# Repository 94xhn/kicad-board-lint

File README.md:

# kicad-board-lint

A zero-dependency linter for the board problems **KiCad's DRC silently
accepts**: copper pads with no net, duplicate pads that disagree about their
net, and power tracks too thin for their current. No KiCad installation, no
pcbnew bindings — it parses `.kicad_pcb` / `.kicad_pro` directly, so it runs
anywhere Python runs, including CI.

[中文简介](#中文简介) below. Part of a small family of KiCad lint tools:
[kicad-corner-lint](https://github.com/94xhn/kicad-corner-lint) ·
[kicad-file-doctor](https://github.com/94xhn/kicad-file-doctor).

```text
$ kicad-board-lint examples/demo.kicad_pcb
examples/demo.kicad_pcb: 4 footprints, 4 segments - 4 error(s), 1 warning(s)
  ERROR   dup-pad-net     SW1: duplicate pads "1" disagree about their net: "COL1" vs <none>
  ERROR   ghost-pad       SW1 pad 1 has no net (DRC will not flag this)  at (122.900, 97.750) mm
  ERROR   ghost-pad       U1 pad 3 has no net (DRC will not flag this)  at (111.150, 100.000) mm
  ERROR   power-width     net "+5V": 2 of 3 segment(s) narrower than 1.5mm (worst 0.25mm at (100.0, 100.0) mm; netclass HighCurrent; DRC does not check current capacity)  at (100.000, 100.000) mm
  WARNING netclass-orphan netclass "HighCurrent" assigns net "+12V" but the board has no such net (it silently falls back to Default)
FAIL: 4 error(s), 1 warning(s) across 1 file(s)
```

## Why — three DRC blind spots

**A pad with no net passes DRC.** KiCad treats a netless copper pad as
standalone copper: it neither needs a connection nor counts as a short, so
the report stays green while the board is wrong. Real ways pads end up
netless:

- a **stale netlist** — you renamed a reference in the schematic, re-ran the
  PCB sync script without re-exporting the netlist, and every pad of that
  part silently lost its net;
- a **symbol with fewer pins than the footprint has pads** — a 2-pin crystal
  symbol on a 4-pad 3225 footprint leaves the housing-ground pads floating
  (the first real board we ran this on had exactly that);
- **duplicate pad numbers** — tactile switches, SOT-223 tabs and thermal
  pads repeat pad numbers, and some toolpaths assign the net to only one of
  the group; autorouters then treat the rest as `<no net>` obstacles and
  short against them.

`ghost-pad` and `dup-pad-net` catch all three.

**A 0.25 mm track carrying 3 A passes DRC.** DRC checks clearance, never
current capacity. `power-width` compares every segment of your power nets
against an expected width from (in increasing precedence): your `.kicad_pro`
net classes, explicit `--rule` patterns, or `--current` ratings converted
through the IPC-2221 outer-layer formula. As a bonus, `netclass-orphan`
flags net-class entries that match no net on the board — the classic
`+5V` vs `/+5V` prefix trap that makes a net class silently fall back to
Default, with a *did-you-mean* suggestion.

## Install

```bash
pip install git+https://github.com/94xhn/kicad-board-lint
```

## Usage

```bash
# run everything; netclass widths picked up from MAIN.kicad_pro automatically
kicad-board-lint MAIN.kicad_pcb

# only the pad checks
kicad-board-lint MAIN.kicad_pcb --check ghost-pads

# expected widths without a .kicad_pro: by pattern, or by current (IPC-2221)
kicad-board-lint MAIN.kicad_pcb --rule "VBAT=0.8" --current "MOTOR*=4.0"

# exempt pad-escape stubs shorter than 2 mm from the width check
kicad-board-lint MAIN.kicad_pcb --min-segment 2

# machine-readable; exit code 1 on any error
kicad-board-lint MAIN.kicad_pcb --format json
```

| Check | Severity | What it means |
|---|---|---|
| `ghost-pad` | error | copper pad with no net — DRC will never tell you |
| `dup-pad-net` | error | same-numbered pads in one footprint disagree about their net |
| `power-width` | error | segments of a power net narrower than expected (one finding per net, worst segment located) |
| `netclass-orphan` | warning | a net-class entry matches nothing on the board (silent fallback to Default) |

Exit codes: `0` clean, `1` errors found (warnings too with `--strict`),
`2` usage/file error.

### Notes on tuning

- **`--min-segment 2`** is the pragmatic switch: escape stubs out of
  fine-pitch IC pads are necessarily narrower than the net's bulk width, and
  a short neck is accepted practice. Without it you will see every escape;
  with it you see only long thin runs — the ones that actually heat up.
- Mounting holes, logos and other `board_only` footprints are skipped
  automatically; use `--ignore-ref "FID*"` for anything else.
- Some boards legitimately leave mechanically-named pads netless —
  connector mounting pins (`MP`), shields, BGA NC balls; KiCad's own demo
  boards include several. Silence them with `--ignore-pad MP` (matches the
  pad *number*). The highest-suspicion pattern remains a footprint where
  *some* pads have nets and others don't.
- IPC-2221 parameters: `--delta-t` (default 10 °C) and `--copper-oz`
  (default 1 oz). Vias and zone fills are not checked (see limitations).

### CI

```yaml
- name: Board lint
  run: |
    pip install git+https://github.com/94xhn/kicad-board-lint
    kicad-board-lint hardware/*.kicad_pcb --min-segment 2
```

### pre-commit

```yaml
repos:
  - repo: https://github.com/94xhn/kicad-board-lint
    rev: v0.1.0
    hooks:
      - id: kicad-board-lint
        args: ["--min-segment", "2"]
```

### Python API

```python
from kicad_board_lint import load_board, check_ghost_pads

board = load_board(open("MAIN.kicad_pcb", encoding="utf-8").read())
for f in check_ghost_pads(board):
    print(f.severity, f.message)
```

## Compatibility

- **KiCad 5 through 10**, including the KiCad 10 format change where pads
  and segments store the net *name* directly (older formats store a numeric
  id resolved through the board's net table — both are handled).
- Net-class expectations are read from `.kicad_pro`: `netclass_patterns`
  (the KiCad 7+ form — both wildcard and regex patterns are matched, like
  KiCad itself does) plus legacy `classes[].nets` arrays (pre-v3 schema,
  still written by some external tools; KiCad migrates them on load).
- Python ≥ 3.9, any OS, zero dependencies.

## Known limitations (v0.1)

- **Vias are not checked** for current capacity (different physics —
  planned).
- **Zone fills are not checked**; a net carried by a pour is judged only by
  its discrete segments.
- `power-width` needs an expectation source; without `.kicad_pro` classes,
  `--rule` or `--current`, it has nothing to compare against and stays
  silent.
- **Legacy boards over-report on `ghost-pads`**: on boards last saved by
  old KiCad versions (5.x era), pads the schematic legitimately leaves
  unconnected may carry no net at all — the per-pad `unconnected-(...)`
  net convention is newer. The check is calibrated for KiCad 7+ boards;
  on older ones expect noise or use `--check power-width` only.
  Measured on KiCad's own demo set: modern boards (StickHub, tiny_tapeout,
  sonde) report **zero** findings and recent boards report 1–2, while
  legacy-era boards (video, vme-wren) report dozens — that gap is the era
  difference, not parser noise.

## Related tools

- [kicad-corner-lint](https://github.com/94xhn/kicad-corner-lint) — flags
  right-angle and acute track corners (same zero-dependency family).
- [kicad-file-doctor](https://github.com/94xhn/kicad-file-doctor) — explains
  why KiCad rejects or mis-loads a file.
- [rjwalters/kicad-tools](https://github.com/rjwalters/kicad-tools) has a
  geometric `--trace-width` minimum check; this tool instead checks
  *per-net* expectations sourced from net classes or IPC-2221 current
  ratings.
- KiBot drives KiCad's own DRC — which is exactly the check that misses
  these problems.

## 中文简介

零依赖的 KiCad 板级 lint，专查 **DRC 静默放过**的三类问题：

- **幽灵焊盘**（`ghost-pad`/`dup-pad-net`）：焊盘没有网络时 KiCad 把它当
  "独立铜"，DRC 完全不报。netlist 过期后同步脚本静默跳过、符号引脚数少于
  封装焊盘数（如 2 脚晶振符号配 4 焊盘 3225 封装，外壳地悬空）、同号焊盘
  （轻触开关/SOT-223 散热脚）只有一个分到网络——三类真实事故一个检查全收。
- **电源线宽**（`power-width`）：DRC 只查间距不查载流。期望宽度三种来源：
  `.kicad_pro` netclass、`--rule` 通配、`--current` 电流值（IPC-2221 反算）。
  `--min-segment 2` 可豁免 IC 引脚逃逸短颈。
- **netclass 静默失效**（`netclass-orphan`）：netclass 里 net 名写错（典型
  `/+5V` 前缀坑）会静默回落 Default 细线——本工具直接给出 did-you-mean。

```bash
pip install git+https://github.com/94xhn/kicad-board-lint
kicad-board-lint 你的板.kicad_pcb --min-segment 2
```

兼容 KiCad 5–10；纯 Python 零依赖，可直接进 CI。同家族工具：
[kicad-corner-lint](https://github.com/94xhn/kicad-corner-lint)（直角/锐角
走线检测）、[kicad-file-doctor](https://github.com/94xhn/kicad-file-doctor)
（文件加载失败诊断）。

## License

[MIT](LICENSE)

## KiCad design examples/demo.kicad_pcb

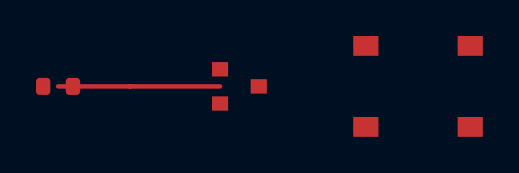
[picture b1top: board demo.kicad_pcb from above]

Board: 2 copper layers, 4 parts (0 on the bottom side), 2 nets.

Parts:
MH1: MountingHole_3.2mm_M3
R1: R_0603
SW1: SW_SPST_TL3342
U1: SOT-23

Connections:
+5V: R1.1, U1.1
GND: R1.2, U1.2
